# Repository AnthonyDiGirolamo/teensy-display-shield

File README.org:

* teensy-display-shield

  Handheld [[https://excamera.com/sphinx/gameduino3/][Gameduino3]] display shield for the [[https://www.pjrc.com/store/teensy41.html][Teensy 4.1]], [[https://www.pjrc.com/store/teensy36.html][3.6]] or [[https://www.adafruit.com/category/946][Adafruit Feather form
  factor boards]].

  [[./images/v0_assembled1.jpg]]

  [[./images/v0_component_placement1.jpg]]

** Version 0

*** Features

    - Teensy and Feather headers.
    - Arduino shield header for use with a Gameduino3 screen.
    - USB-A host jack for Teensy 3.6 and 4.1 boards. For plugging in an external
      keyboard, mouse, or controller.
    - 3v coin cell footprint for Teensy RTC.
    - Through hole buttons for up, down, left, right, a, b, x, y, start, select.
    - On board power:
      - LiPo charging using the [[https://lcsc.com/product-detail/PMIC-Battery-Management_TOPPOWER-Nanjing-Extension-Microelectronics-TP4054_C32574.html][TP4054]] (at 500mA charge-rate).
      - 5 volt boost regulator using the [[https://lcsc.com/product-detail/DC-DC-Converters_Feeling-Tech-FP6291LR-G1_C18701.html][FP6291]]. This powers the Gameduino3 and Teensy.
      - Load sharing between USB and charging.
      - Battery power slide switch.

*** Eratta

    Charging the battery won't work with the power switch in the off
    positon. One cut and jumper wire is needed. See these images:

    [[./images/v0_bodge1.jpg]]

    [[./images/v0_bodge2.jpg]]

** Version 1

*** Required Fixes
    - Correct missing silkscreen pin labels
    - Make all through hole GND connections square pads.

*** Planned Features
    - Push-button on/off operation using [[https://web.archive.org/web/20201001131408/http://www.mosaic-industries.com/embedded-systems/microcontroller-projects/electronic-circuits/push-button-switch-turn-on/microcontroller-latching-on-off][this schematic]].
    - L and R shoulder buttons.
    - Analog sticks?
    - [[https://www.crowdsupply.com/excamera/gameduino-3x-dazzler][Gameduino 3X Dazzler]] surface mount footprint.
    - Display panel FPC connector and backlight driver.
    - Solder jumpers to control battery charge rate.

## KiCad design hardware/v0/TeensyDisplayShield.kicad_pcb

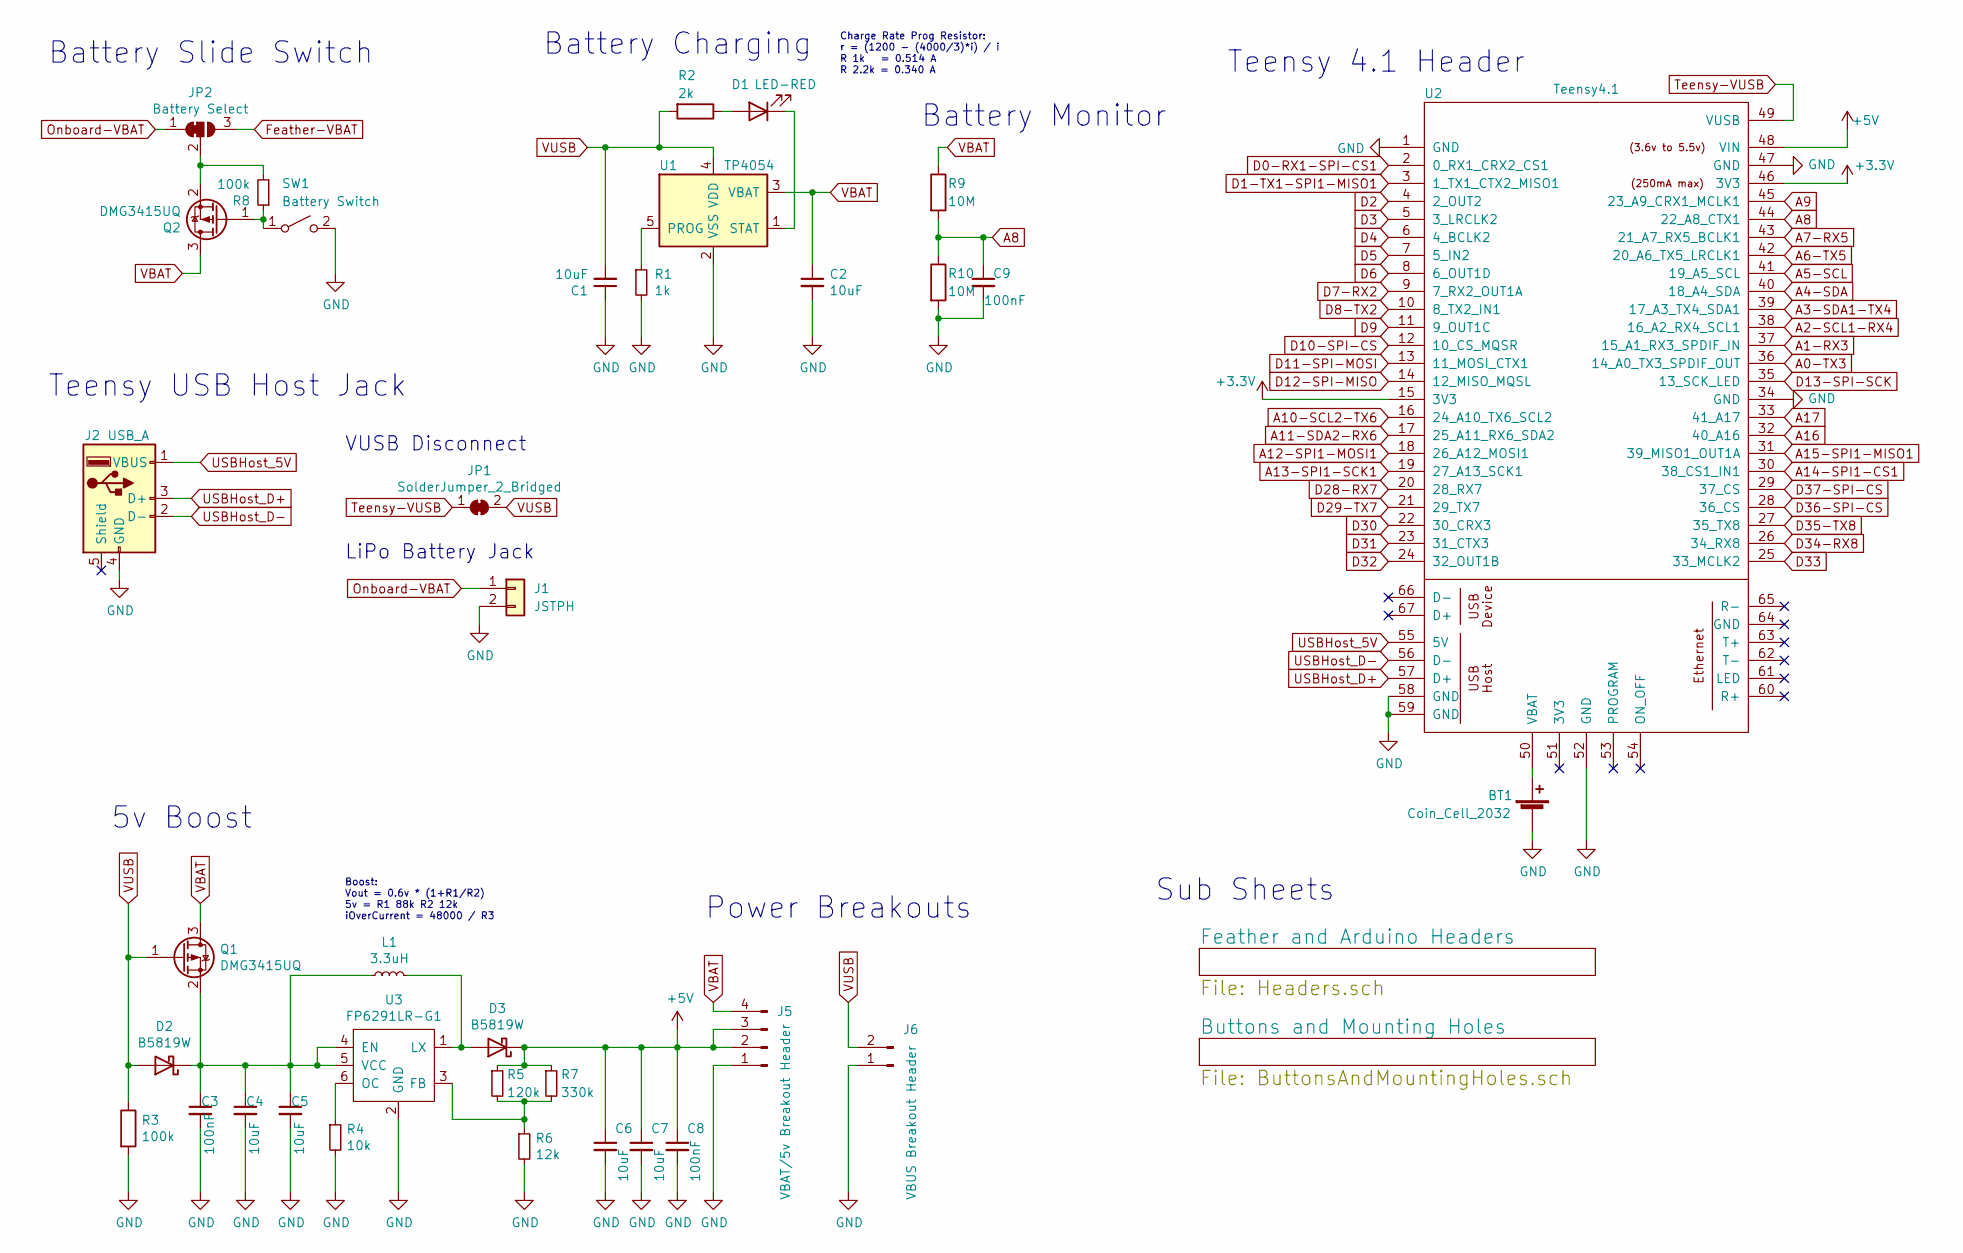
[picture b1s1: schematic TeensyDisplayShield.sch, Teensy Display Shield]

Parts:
BT1: Coin_Cell_2032; CoinCell2032HarwinS8421-45R-HandSolder
C1, C2, C4, C5, C6, C7: 10uF; C_1206_3216Metric_Pad1.33x1.80mm_HandSolder; LCSC C13585
C3, C8, C9: 100nF; C_1206_3216Metric_Pad1.33x1.80mm_HandSolder; LCSC C24497
D1: LED-RED; LED_0603_1608Metric_Pad1.05x0.95mm_HandSolder; LCSC C2286
D2, D3: B5819W; D_SOD-123; LCSC C8598
J1: JSTPH; JST_PH_S2B-PH-K_1x02_P2.00mm_Horizontal
J2: USB_A; USB_A_Molex_67643_Horizontal
J5: VBAT/5v Breakout Header; PinHeader_1x04_P2.54mm_Vertical
J6: VBUS Breakout Header; PinHeader_1x02_P2.54mm_Vertical
JP1: SolderJumper_2_Bridged; SolderJumper-2_P1.3mm_Bridged2Bar_Pad1.0x1.5mm
JP2: Battery Select; SolderJumper-3_P1.3mm_Bridged12_Pad1.0x1.5mm
L1: 3.3uH; L_Sunlord_MWSA0518_5.4x5.2mm; LCSC C408336
Q1, Q2: DMG3415UQ; SOT-23; LCSC C459537
R1: 1k; R_0603_1608Metric_Pad0.98x0.95mm_HandSolder; LCSC C21190
R2: 2k; R_0603_1608Metric_Pad0.98x0.95mm_HandSolder; LCSC C22975
R3, R8: 100k; R_0603_1608Metric_Pad0.98x0.95mm_HandSolder; LCSC C25803
R4: 10k; R_0603_1608Metric_Pad0.98x0.95mm_HandSolder; LCSC C25804
R5: 120k; R_0603_1608Metric_Pad0.98x0.95mm_HandSolder; LCSC C25808
R6: 12k; R_0603_1608Metric_Pad0.98x0.95mm_HandSolder; LCSC C22790
R7: 330k; R_0603_1608Metric_Pad0.98x0.95mm_HandSolder; LCSC C23137
R9, R10: 10M; R_0603_1608Metric_Pad0.98x0.95mm_HandSolder; LCSC C7250
SW1: Battery Switch; PinHeader_1x03_P2.54mm_Vertical
U1: TP4054; SOT-23-5; LCSC C32574
U2: Teensy4.1; Teensy41NoEthernet
U3: FP6291LR-G1; SOT-23-6; LCSC C18701

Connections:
+5V: C6.1, C7.1, C8.1, D3.1 (K), J5.2, J5.3, R5.1, R7.1, U2.48 (VIN); also elsewhere on the board
A0-TX3: U2.36 (14_A0_TX3_SPDIF_OUT); also elsewhere on the board
A1-RX3: U2.37 (15_A1_RX3_SPDIF_IN); also elsewhere on the board
A2-SCL1-RX4: U2.38 (16_A2_RX4_SCL1); also elsewhere on the board
A3-SDA1-TX4: U2.39 (17_A3_TX4_SDA1); also elsewhere on the board
A4-SDA: U2.40 (18_A4_SDA); also elsewhere on the board
A5-SCL: U2.41 (19_A5_SCL); also elsewhere on the board
A6-TX5: U2.42 (20_A6_TX5_LRCLK1); also elsewhere on the board
A7-RX5: U2.43 (21_A7_RX5_BCLK1); also elsewhere on the board
A8: C9.1, R9.2, R10.1, U2.44 (22_A8_CTX1); also elsewhere on the board
A9: U2.45 (23_A9_CRX1_MCLK1); also elsewhere on the board
A10-SCL2-TX6: U2.16 (24_A10_TX6_SCL2); also elsewhere on the board
A11-SDA2-RX6: U2.17 (25_A11_RX6_SDA2); also elsewhere on the board
A12-SPI1-MOSI1: U2.18 (26_A12_MOSI1)
A13-SPI1-SCK1: U2.19 (27_A13_SCK1)
A14-SPI1-CS1: U2.30 (38_CS1_IN1)
A15-SPI1-MISO1: U2.31 (39_MISO1_OUT1A)
A16: U2.32 (40_A16); also elsewhere on the board
A17: U2.33 (41_A17); also elsewhere on the board
Button-B: U2.23 (31_CTX3); also elsewhere on the board
Button-Down: U2.5 (3_LRCLK2); also elsewhere on the board
Button-Left: U2.6 (4_BCLK2); also elsewhere on the board
Button-Right: U2.7 (5_IN2); also elsewhere on the board
Button-Select: U2.8 (6_OUT1D); also elsewhere on the board
Button-Up: U2.4 (2_OUT2); also elsewhere on the board
Button-Y: U2.22 (30_CRX3); also elsewhere on the board
D0-RX1-SPI-CS1: U2.2 (0_RX1_CRX2_CS1); also elsewhere on the board
D1-TX1-SPI1-MISO1: U2.3 (1_TX1_CTX2_MISO1); also elsewhere on the board
D7-RX2: U2.9 (7_RX2_OUT1A)
D8-TX2: U2.10 (8_TX2_IN1); also elsewhere on the board
D9: U2.11 (9_OUT1C); also elsewhere on the board
D10-SPI-CS: U2.12 (10_CS_MQSR); also elsewhere on the board
D11-SPI-MOSI: U2.13 (11_MOSI_CTX1); also elsewhere on the board
D12-SPI-MISO: U2.14 (12_MISO_MQSL); also elsewhere on the board
D13-SPI-SCK: U2.35 (13_SCK_LED); also elsewhere on the board
D28-RX7: U2.20 (28_RX7); also elsewhere on the board
D29-TX7: U2.21 (29_TX7); also elsewhere on the board
D32: U2.24 (32_OUT1B)
D33: U2.25 (33_MCLK2)
D34-RX8: U2.26 (34_RX8); also elsewhere on the board
D35-TX8: U2.27 (35_TX8); also elsewhere on the board
D36-SPI-CS: U2.28 (36_CS)
D37-SPI-CS: U2.29 (37_CS)
Feather-VBAT: JP2.3 (B); also elsewhere on the board
GND: BT1.2 (-), C1.1, C2.2, C3.2, C4.2, C5.2, C6.2, C7.2, C8.2, C9.2, J1.2, J2.4 (GND), J5.1, J6.1, R1.2, R3.2, R4.2, R6.2, R10.2, SW1.2 (B), U1.2 (VSS), U2.1 (GND), U2.34 (GND), U2.47 (GND), U2.52 (GND), U2.58 (GND), U2.59 (GND), U3.2 (GND); also elsewhere on the board
unnamed: BT1.1 (+), U2.50 (VBAT)
unnamed: C3.1, C4.1, C5.1, D2.1 (K), L1.1, Q1.2 (S), U3.4 (EN), U3.5 (VCC)
unnamed: D1.1 (K), U1.1 (STAT)
unnamed: D1.2 (A), R2.1
unnamed: D3.2 (A), L1.2, U3.1 (LX)
unnamed: JP2.2 (C), Q2.2 (S), R8.2
unnamed: Q2.1 (G), R8.1, SW1.1 (A)
unnamed: R1.1, U1.5 (PROG)
unnamed: R4.1, U3.6 (OC)
unnamed: R5.2, R6.1, R7.2, U3.3 (FB)
Onboard-VBAT: J1.1, JP2.1 (A)
Teensy-VUSB: JP1.1 (A), U2.49 (VUSB)
USBHost_5V: J2.1 (VBUS), U2.55 (5V)
USBHost_D+: J2.3 (D+), U2.57 (D+)
USBHost_D-: J2.2 (D-), U2.56 (D-)
VBAT: C2.1, J5.4, Q1.3 (D), Q2.3 (D), R9.1, U1.3 (VBAT)
VUSB: C1.2, D2.2 (A), J6.2, JP1.2 (B), Q1.1 (G), R2.2, R3.1, U1.4 (VDD)

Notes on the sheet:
Teensy 4.1 Header
5v Boost
Boost: Vout = 0.6v * (1+R1/R2) 5v = R1 88k R2 12k iOverCurrent = 48000 / R3
Battery Slide Switch
Charge Rate Prog Resistor: r = (1200 - (4000/3)*i) / i R 1k = 0.514 A R 2.2k = 0.340 A
Battery Charging
Teensy USB Host Jack
VUSB Disconnect
LiPo Battery Jack
Sub Sheets
Battery Monitor
Power Breakouts

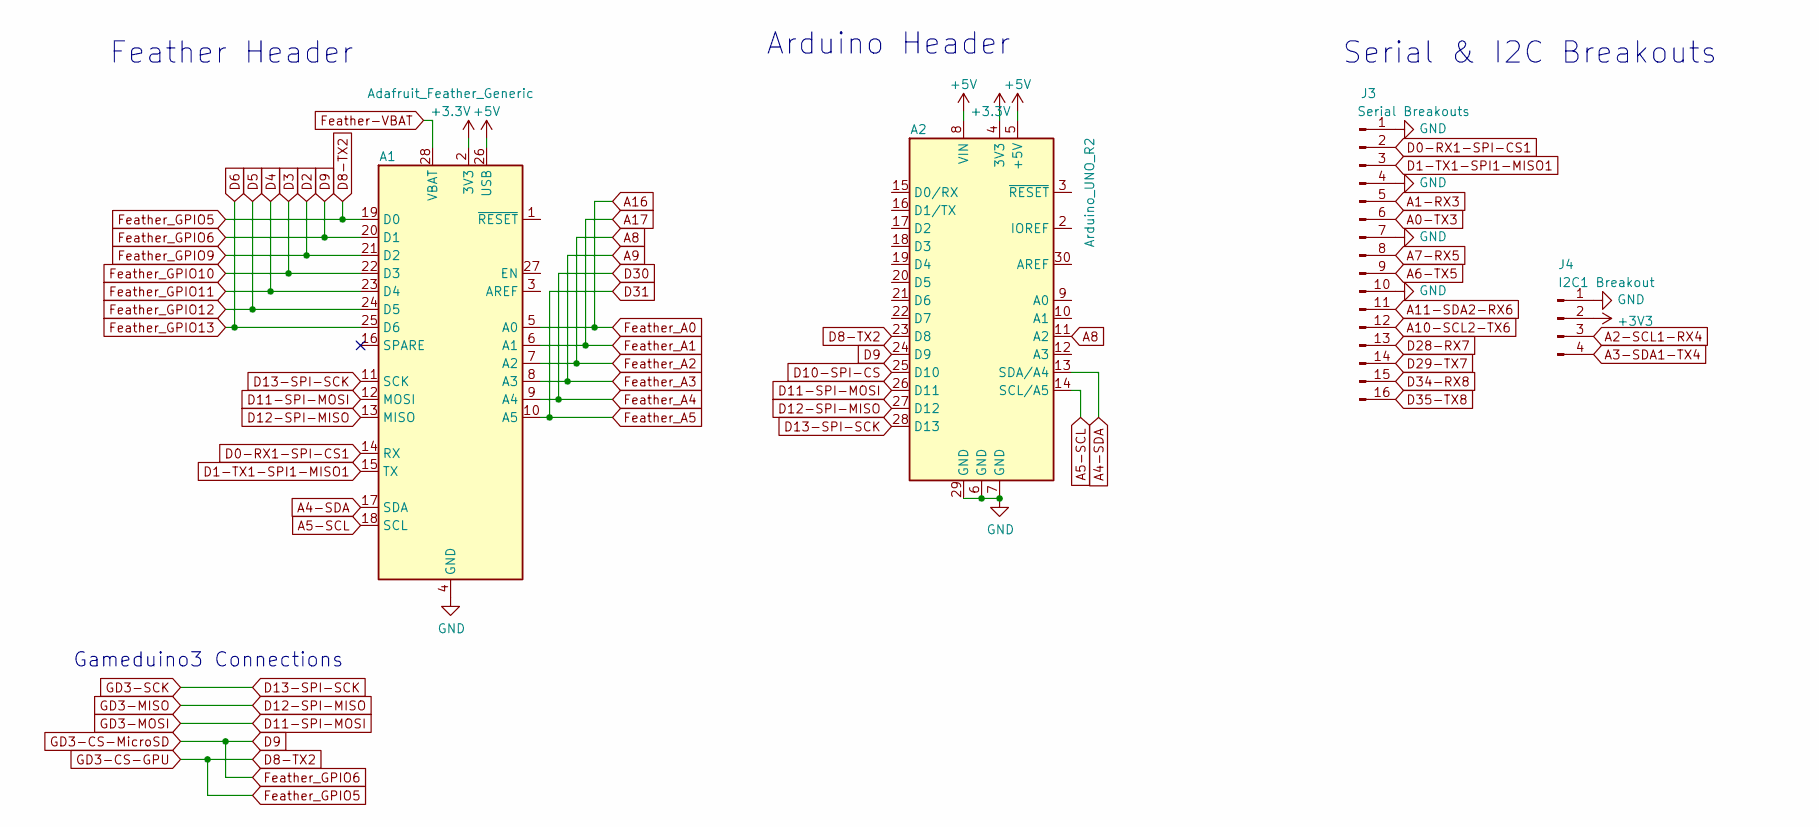
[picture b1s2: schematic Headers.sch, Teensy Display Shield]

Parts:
A1: Adafruit_Feather_Generic; Adafruit_Feather
A2: Arduino_UNO_R2
J3: Serial Breakouts; PinHeader_1x16_P2.54mm_Vertical
J4: I2C1 Breakout; PinHeader_1x04_P2.54mm_Vertical

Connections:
+5V: A1.26 (USB), A2.5 (+5V), A2.8 (VIN); also elsewhere on the board
A0-TX3: J3.6; also elsewhere on the board
A1-RX3: J3.5; also elsewhere on the board
A2-SCL1-RX4: J4.3; also elsewhere on the board
A3-SDA1-TX4: J4.4; also elsewhere on the board
A4-SDA: A1.17 (SDA), A2.13 (SDA/A4); also elsewhere on the board
A5-SCL: A1.18 (SCL), A2.14 (SCL/A5); also elsewhere on the board
A6-TX5: J3.9; also elsewhere on the board
A7-RX5: J3.8; also elsewhere on the board
A8: A1.7 (A2), A2.11 (A2); also elsewhere on the board
A9: A1.8 (A3); also elsewhere on the board
A10-SCL2-TX6: J3.12; also elsewhere on the board
A11-SDA2-RX6: J3.11; also elsewhere on the board
A16: A1.5 (A0); also elsewhere on the board
A17: A1.6 (A1); also elsewhere on the board
Button-B: A1.10 (A5); also elsewhere on the board
Button-Down: A1.22 (D3); also elsewhere on the board
Button-Left: A1.23 (D4); also elsewhere on the board
Button-Right: A1.24 (D5); also elsewhere on the board
Button-Select: A1.25 (D6); also elsewhere on the board
Button-Up: A1.21 (D2); also elsewhere on the board
Button-Y: A1.9 (A4); also elsewhere on the board
D0-RX1-SPI-CS1: A1.14 (RX), J3.2; also elsewhere on the board
D1-TX1-SPI1-MISO1: A1.15 (TX), J3.3; also elsewhere on the board
D8-TX2: A1.19 (D0), A2.23 (D8); also elsewhere on the board
D9: A1.20 (D1), A2.24 (D9); also elsewhere on the board
D10-SPI-CS: A2.25 (D10); also elsewhere on the board
D11-SPI-MOSI: A1.12 (MOSI), A2.26 (D11); also elsewhere on the board
D12-SPI-MISO: A1.13 (MISO), A2.27 (D12); also elsewhere on the board
D13-SPI-SCK: A1.11 (SCK), A2.28 (D13); also elsewhere on the board
D28-RX7: J3.13; also elsewhere on the board
D29-TX7: J3.14; also elsewhere on the board
D34-RX8: J3.15; also elsewhere on the board
D35-TX8: J3.16; also elsewhere on the board
Feather-VBAT: A1.28 (VBAT); also elsewhere on the board
GND: A1.4 (GND), A2.6 (GND), A2.7 (GND), A2.29 (GND), J3.1, J3.4, J3.7, J3.10, J4.1; also elsewhere on the board

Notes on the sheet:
Feather Header
Arduino Header
Gameduino3 Connections
Serial & I2C Breakouts

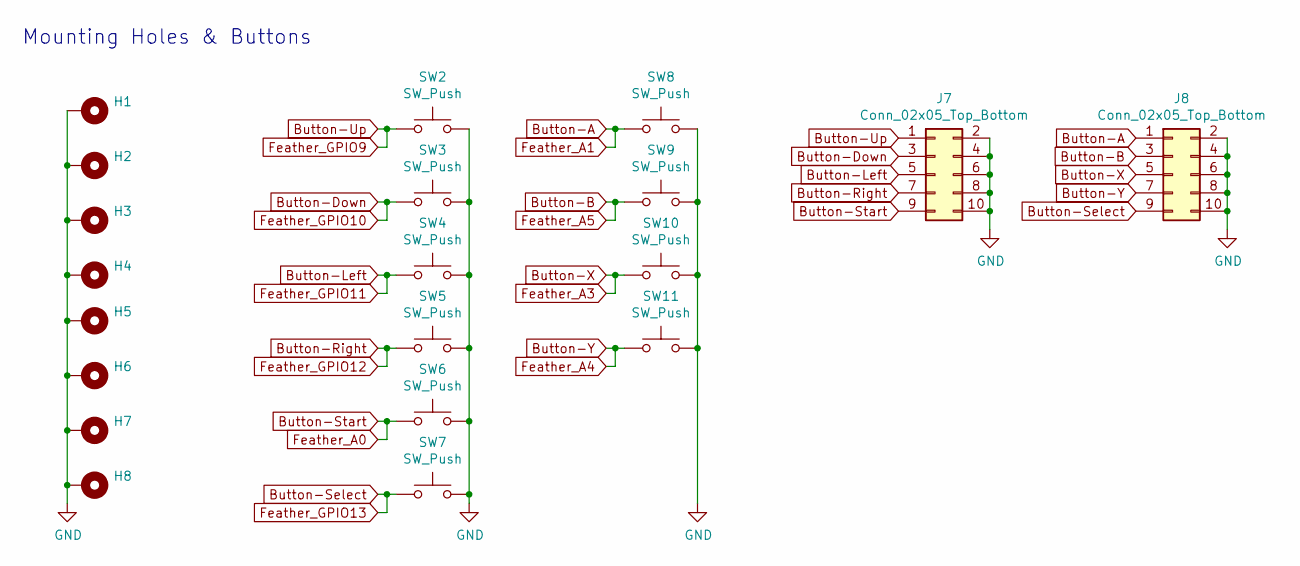
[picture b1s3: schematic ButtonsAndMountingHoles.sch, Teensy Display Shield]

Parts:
H1, H2, H3, H4, H5, H6, H7, H8: MountingHole_Pad; MountingHole_3.2mm_M3_Pad
J7, J8: Conn_02x05_Top_Bottom; PinHeader_2x05_P2.54mm_Vertical
SW2, SW3, SW4, SW5, SW6, SW7, SW8, SW9, SW10, SW11: SW_Push; SW_PUSH_6mm

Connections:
A9: J8.5, SW10.1; also elsewhere on the board
A16: J7.9, SW6.1; also elsewhere on the board
A17: J8.1, SW8.1; also elsewhere on the board
Button-B: J8.3, SW9.1; also elsewhere on the board
Button-Down: J7.3, SW3.1; also elsewhere on the board
Button-Left: J7.5, SW4.1; also elsewhere on the board
Button-Right: J7.7, SW5.1; also elsewhere on the board
Button-Select: J8.9, SW7.1; also elsewhere on the board
Button-Up: J7.1, SW2.1; also elsewhere on the board
Button-Y: J8.7, SW11.1; also elsewhere on the board
GND: H1.1, H2.1, H3.1, H4.1, H5.1, H6.1, H7.1, H8.1, J7.2, J7.4, J7.6, J7.8, J7.10, J8.2, J8.4, J8.6, J8.8, J8.10, SW2.2, SW3.2, SW4.2, SW5.2, SW6.2, SW7.2, SW8.2, SW9.2, SW10.2, SW11.2; also elsewhere on the board

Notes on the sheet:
Mounting Holes & Buttons

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
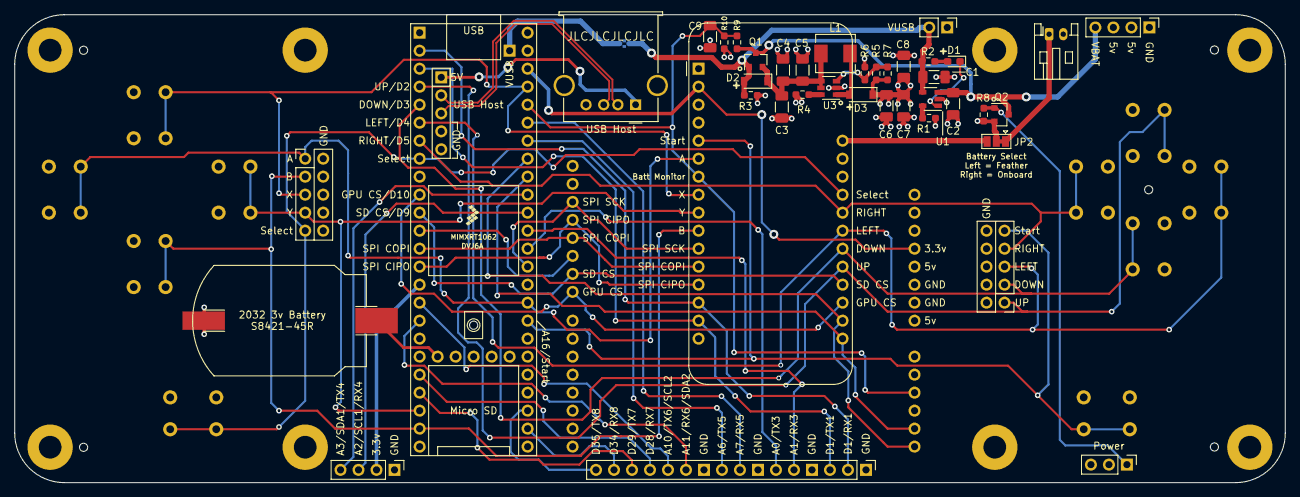
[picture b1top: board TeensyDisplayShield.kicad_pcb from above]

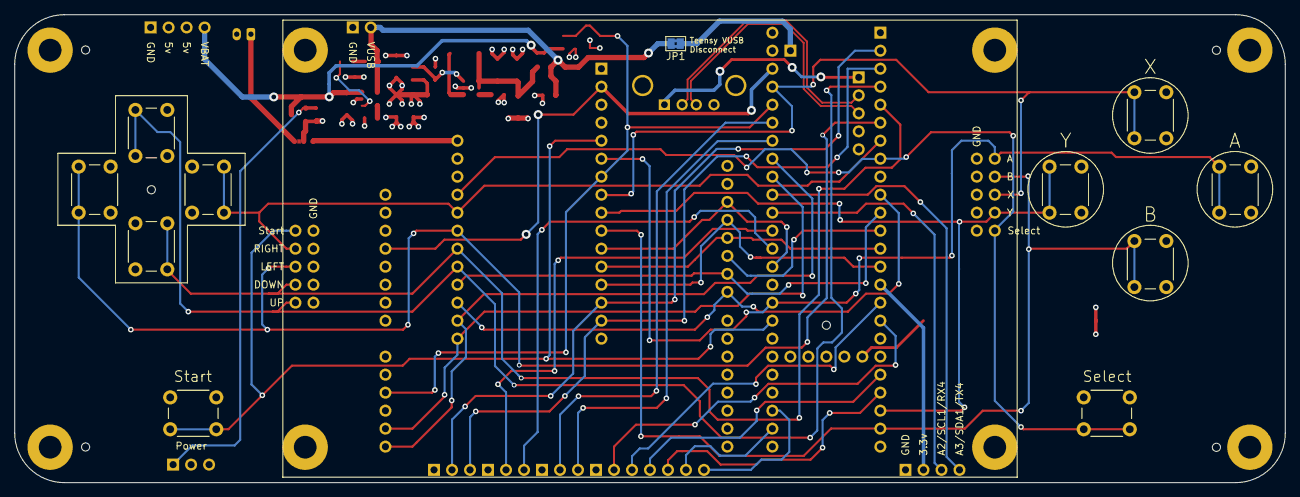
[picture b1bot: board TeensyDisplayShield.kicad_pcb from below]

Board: 4 copper layers, 179.3 x 66.0 mm, 60 parts (11 on the bottom side), 54 nets.

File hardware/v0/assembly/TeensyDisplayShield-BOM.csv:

Comment,Designator,Footprint,LCSC
"Adafruit_Feather_Generic","A1","Module_Latest:Adafruit_Feather",""
"Arduino_UNO_R2","A2","Module_Latest:Arduino_UNO_R2",""
"Coin_Cell_2032","BT1","Teensy:CoinCell2032HarwinS8421-45R-HandSolder",""
"100nF","C3,C8,C9","Capacitor_SMD:C_1206_3216Metric_Pad1.33x1.80mm_HandSolder","C24497"
"10uF","C1,C2,C4,C5,C6,C7","Capacitor_SMD:C_1206_3216Metric_Pad1.33x1.80mm_HandSolder","C13585"
"LED-RED","D1","LED_SMD:LED_0603_1608Metric_Pad1.05x0.95mm_HandSolder","C2286"
"B5819W","D2,D3","Diode_SMD:D_SOD-123","C8598"
"MountingHole_Pad","H1,H2,H3,H4,H5,H6,H7,H8","MountingHole:MountingHole_3.2mm_M3_Pad",""
"JSTPH","J1","Connector_JST:JST_PH_S2B-PH-K_1x02_P2.00mm_Horizontal",""
"USB_A","J2","Connector_USB:USB_A_Molex_67643_Horizontal",""
"Serial Breakouts","J3","Connector_PinHeader_2.54mm:PinHeader_1x16_P2.54mm_Vertical",""
"I2C1 Breakout","J4","Connector_PinHeader_2.54mm:PinHeader_1x04_P2.54mm_Vertical",""
"VBAT/5v Breakout Header","J5","Connector_PinHeader_2.54mm:PinHeader_1x04_P2.54mm_Vertical",""
"VBUS Breakout Header","J6","Connector_PinHeader_2.54mm:PinHeader_1x02_P2.54mm_Vertical",""
"Conn_02x05_Top_Bottom","J7,J8","Connector_PinHeader_2.54mm:PinHeader_2x05_P2.54mm_Vertical",""
"SolderJumper_2_Bridged","JP1","Jumper:SolderJumper-2_P1.3mm_Bridged2Bar_Pad1.0x1.5mm",""
"Battery Select","JP2","Jumper:SolderJumper-3_P1.3mm_Bridged12_Pad1.0x1.5mm",""
"3.3uH","L1","Inductor_SMD:L_Sunlord_MWSA0518_5.4x5.2mm","C408336"
"DMG3415UQ","Q1,Q2","Package_TO_SOT_SMD:SOT-23","C459537"
"1k","R1","Resistor_SMD:R_0603_1608Metric_Pad0.98x0.95mm_HandSolder","C21190"
"10M","R9,R10","Resistor_SMD:R_0603_1608Metric_Pad0.98x0.95mm_HandSolder","C7250"
"2k","R2","Resistor_SMD:R_0603_1608Metric_Pad0.98x0.95mm_HandSolder","C22975"
"100k","R3,R8","Resistor_SMD:R_0603_1608Metric_Pad0.98x0.95mm_HandSolder","C25803"
"10k","R4","Resistor_SMD:R_0603_1608Metric_Pad0.98x0.95mm_HandSolder","C25804"
"120k","R5","Resistor_SMD:R_0603_1608Metric_Pad0.98x0.95mm_HandSolder","C25808"
"12k","R6","Resistor_SMD:R_0603_1608Metric_Pad0.98x0.95mm_HandSolder","C22790"
"330k","R7","Resistor_SMD:R_0603_1608Metric_Pad0.98x0.95mm_HandSolder","C23137"
"Battery Switch","SW1","Connector_PinHeader_2.54mm:PinHeader_1x03_P2.54mm_Vertical",""
"SW_Push","SW2,SW3,SW4,SW5,SW6,SW7,SW8,SW9,SW10,SW11","Button_Switch_THT:SW_PUSH_6mm",""
"TP4054","U1","Package_TO_SOT_SMD:SOT-23-5","C32574"
"Teensy4.1","U2","Teensy:Teensy41NoEthernet",""
"FP6291LR-G1","U3","Package_TO_SOT_SMD:SOT-23-6","C18701"

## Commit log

2021-02-11 Add v0 kicad, photos, and terminal test code.
2021-02-11 Remove unneded files
2021-02-11 Readme formatting.
2021-02-14 Update Terminal class API, fix Munch for 800x480 screens
2021-02-14 More terminal changes
2021-02-14 GD2Terminal class and USB Host Example code
    USB Host example from:
    https://github.com/PaulStoffregen/USBHost_t36
